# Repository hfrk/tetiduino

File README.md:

# Tetiduino
Yet another Arduino UNO clone...

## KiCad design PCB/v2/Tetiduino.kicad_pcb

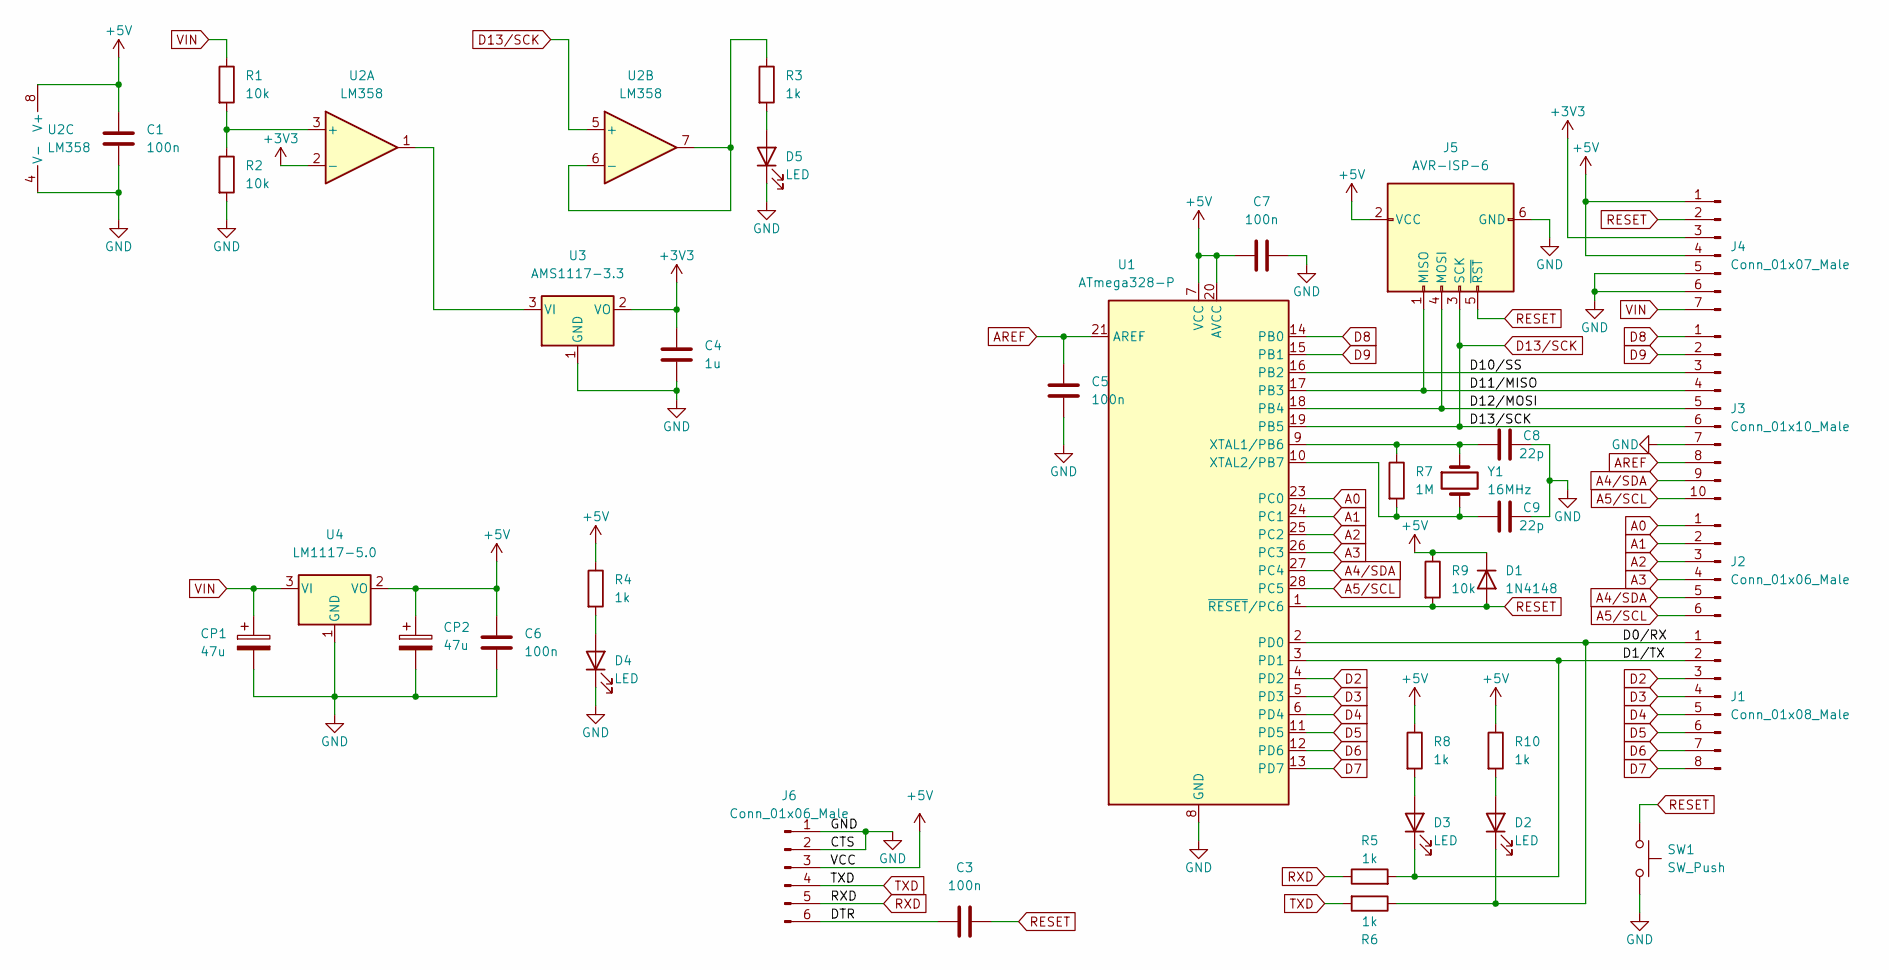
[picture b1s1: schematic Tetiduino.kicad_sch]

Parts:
C1, C3, C5, C6, C7: 100n; C_Axial_L3.8mm_D2.6mm_P7.50mm_Horizontal
C4: 1u; C_Axial_L3.8mm_D2.6mm_P7.50mm_Horizontal
C8, C9: 22p; C_Disc_D3.0mm_W1.6mm_P2.50mm
CP1, CP2: 47u; CP_Radial_D6.3mm_P2.50mm
D1: 1N4148; D_DO-35_SOD27_P7.62mm_Horizontal
D2, D3, D4, D5: LED; LED_D5.0mm
J1: Conn_01x08_Male; PinSocket_1x08_P2.54mm_Vertical
J2, J6: Conn_01x06_Male; PinSocket_1x06_P2.54mm_Vertical
J3: Conn_01x10_Male; PinSocket_1x10_P2.54mm_Vertical
J4: Conn_01x07_Male; PinSocket_1x07_P2.54mm_Vertical
J5: AVR-ISP-6; PinHeader_2x03_P2.54mm_Vertical
R1, R2, R9: 10k; R_Axial_DIN0204_L3.6mm_D1.6mm_P7.62mm_Horizontal
R3, R4, R5, R6, R8, R10: 1k; R_Axial_DIN0204_L3.6mm_D1.6mm_P7.62mm_Horizontal
R7: 1M; R_Axial_DIN0204_L3.6mm_D1.6mm_P7.62mm_Horizontal
SW1: SW_Push; SW_PUSH_6mm
U1: ATmega328-P; DIP-28_W7.62mm
U2: LM358; DIP-8_W7.62mm
U3: AMS1117-3.3; SOT-223-3_TabPin2
U4: LM1117-5.0; TO-220-3_Vertical
Y1: 16MHz; Crystal_HC49-4H_Vertical

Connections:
+3V3: C4.1, J4.3, U2.2 (-), U3.2 (VO)
+5V: C1.1, C6.1, C7.1, CP2.1, D1.1 (K), J4.1, J4.4, J5.2 (VCC), J6.3, R4.1, R8.1, R9.1, R10.1, U1.7 (VCC), U1.20 (AVCC), U2.8 (V+), U4.2 (VO)
/D0/RX: D2.1 (K), J1.1, R6.1, U1.2 (PD0)
/D1/TX: D3.1 (K), J1.2, R5.2, U1.3 (PD1)
/D10/SS: J3.3, U1.16 (PB2)
/D11/MISO: J3.4, J5.1 (MISO), U1.17 (PB3)
/D12/MOSI: J3.5, J5.4 (MOSI), U1.18 (PB4)
/DTR: C3.2, J6.6
A0: J2.1, U1.23 (PC0)
A1: J2.2, U1.24 (PC1)
A2: J2.3, U1.25 (PC2)
A3: J2.4, U1.26 (PC3)
A4/SDA: J2.5, J3.9, U1.27 (PC4)
A5/SCL: J2.6, J3.10, U1.28 (PC5)
AREF: C5.1, J3.8, U1.21 (AREF)
D2: J1.3, U1.4 (PD2)
D3: J1.4, U1.5 (PD3)
D4: J1.5, U1.6 (PD4)
D5: J1.6, U1.11 (PD5)
D6: J1.7, U1.12 (PD6)
D7: J1.8, U1.13 (PD7)
D8: J3.1, U1.14 (PB0)
D9: J3.2, U1.15 (PB1)
D13/SCK: J3.6, J5.3 (SCK), U1.19 (PB5), U2.5 (+)
GND: C1.2, C4.2, C5.2, C6.2, C7.2, C8.2, C9.1, CP1.2, CP2.2, D4.1 (K), D5.1 (K), J3.7, J4.5, J4.6, J5.6 (GND), J6.1, J6.2, R2.2, SW1.2, U1.8 (GND), U1.22 (GND), U2.4 (V-), U3.1 (GND), U4.1 (GND)
unnamed: C8.1, R7.1, U1.9 (XTAL1/PB6), Y1.1
unnamed: C9.2, R7.2, U1.10 (XTAL2/PB7), Y1.2
unnamed: D2.2 (A), R10.2
unnamed: D3.2 (A), R8.2
unnamed: D4.2 (A), R4.2
unnamed: D5.2 (A), R3.2
unnamed: R1.2, R2.1, U2.3 (+)
unnamed: R3.1, U2.6 (-), U2.7
unnamed: U2.1, U3.3 (VI)
RESET: C3.1, D1.2 (A), J4.2, J5.5 (~RST), R9.2, SW1.1, U1.1 (~RESET/PC6)
RXD: J6.5, R5.1
TXD: J6.4, R6.2
VIN: CP1.1, J4.7, R1.1, U4.3 (VI)

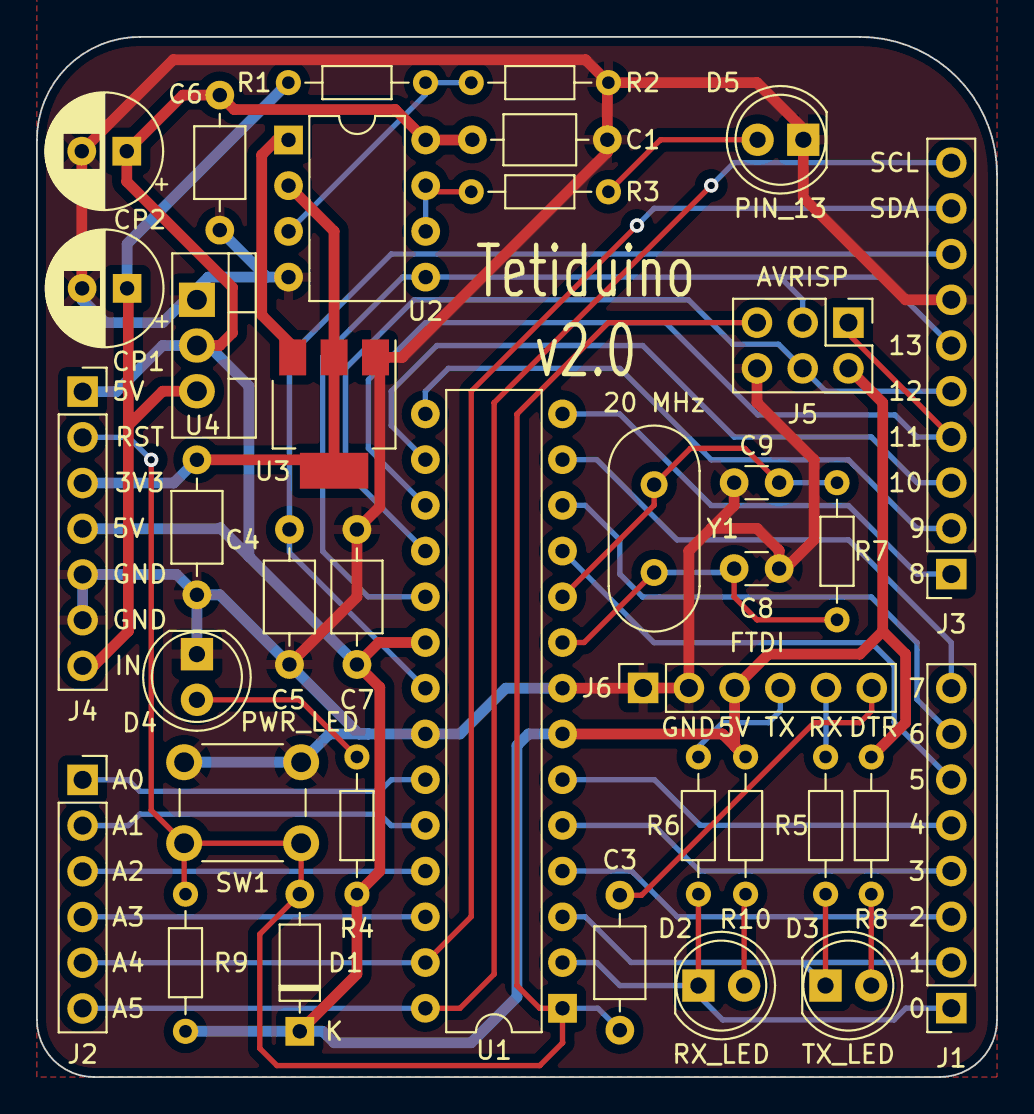
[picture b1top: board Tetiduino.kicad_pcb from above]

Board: 2 copper layers, 53.3 x 57.8 mm, 37 parts (0 on the bottom side), 38 nets.

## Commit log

2023-02-21 First commit.
2023-02-21 Test build the bootloader.
2023-02-21 Bump package.json to test bootloader build.
2023-02-21 Remove stray comma.
2023-02-21 Remove another stray comma.
2023-02-21 Bump package.json again to test bootloader build.
2023-02-21 Bump version.
2023-03-06 Add option for optiboot v8.3, v4.4, and blank bootloader.
2023-03-06 Bump package.json to v0.0.3.
2023-03-16 Update .gitignore.
2023-03-16 Change menu.cpu to menu.bootloader.
2023-03-21 Start building tetiboot bootloader, currently very basic jump-to-app on boot.
2023-03-21 Add blink LED for bootloader testing.
2023-04-05 Add v2 PCBs, uses FTDI module instead of direct USB connection.
2023-05-18 Fixed PCBs for production.
2023-05-18 First working bootloader.
2023-05-18 Change makefile to enable use of 20 MHz crystal.
2023-06-08 Adjust and simplify makefile.
2023-06-08 Add spmlpm.h as new file.
